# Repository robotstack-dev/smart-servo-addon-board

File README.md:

# Smart Servo Add-on Board

This repository contains the hardware design files and documentation for the Smart Servo Add-On Board.

[**Buy on Tindie**](https://www.tindie.com/products/robotstack/smart-servo-addon-board/)

> **Note:** This is an early version of the board. While it has been tested with several servo models, bugs may exist. Please report any issues you encounter.

## Description

This board allows wireless control different TTL smart servos. I developed it to use with Seeed's Xiao esp32-s3 Microcontroller, but it should also work with Adafruit's QT-Py esp32-s3, and likely other esp32s. I've tested it with the following smart servos: Robotis XL430-W250, AX-12W, Feetech HL3930M, and briefly with Waveshare's ST3215. Firmware and Control Software are available in the links below.

<div style="text-align: center;">
    
</div>

## Features

- Wireless Control of Smart Servos
- Compatible with Seeed Xiao and Adafruit QT-Py Form Factor
- Connectors for:

  - Dynamixel X-Series
  - Dynamixel AX-Series
  - Feetech HLS-Series / Waveshare ST3215

  > (Likely compatible with other smart servos; check your servo's specs)

- Stemma QT / QWIIC connector for compatible daughter boards (ie. sensors)
- Breakout pins
- 6.5 to 12 Volt Supply Range (check servo documentation for requirements)
- On board 5V regulator for Microcontroller
- Reverse Polarity Protection
- Firmware and Control Software available

## Hardware Overview

The pinouts are determined by the microcontroller you use. This board was designed to be used with the Seeed Xiao ESP32-S3 or the Adafruit QT Py ESP32-S3. See their documentation for details.

> **Important**: Check your servo connector's pinouts before connecting! Connecting to the wrong connector could damage the board and your servo.

<div style="text-align: center;">

</div>

<div style="text-align: center;">
    
</div>

<div style="text-align: center;">
    
</div>

## Getting the Board

### Pre-assembled

Pre-assembled boards are available for purchase on Tindie:
[Buy on Tindie](https://www.tindie.com/products/robotstack/smart-servo-addon-board/)

### DIY

You can build this board yourself using the hardware design files in this repository.

## Firmware

Example firmware for this board is available in a separate Arduino library. You can find it here:
[Smart Servo Bridge](https://github.com/robotstack-dev/smart-servo-bridge)

The library can be used with or without this addon board, making it flexible for different applications.

## Control Software

Python SDKs enabling wireless control of your smart servos are available. They require use of these boards implementing the [Smart Servo Bridge](https://github.com/robotstack-dev/smart-servo-bridge) library, or similar:

- [FTServo Python Websockets](https://github.com/robotstack-dev/ftservo-python-websockets)
- [Dynamixel Python SDK Websockets](https://github.com/robotstack-dev/dynamixel-python-sdk-websockets)

Other smart servos will require similar modifications to their SDKs.

## Getting Started

1. Build or purchase the circuit.
2. Attach a Microcontroller (eg. Seeed Xiao esp32-s3, or Adafruit QT Py esp32-s3).
3. Upload firmware over USB.
4. Attach your smart servo to the correct connector, according to your servo pinout.
5. Attach a power supply between 6.5 and 12 Volts, according to your servo requirements.
6. Run one of the control software examples that corresponds with your servo.

## Contributing

Contributions are welcome! Here are some guidelines to help you get started:

### How to Contribute

1. Fork the repository and create your branch from `master`.
2. Clone your fork and make your changes.
3. Test your changes if possible.
4. Submit a pull request with a clear description of your changes.

### Code of Conduct

- Be respectful and considerate in your communications.
- Assume good intentions and be constructive in feedback.

### Reporting Issues

- Use the issue tracker to report bugs or request features.
- Provide as much detail as possible (steps to reproduce, expected behavior, etc.).

## Author

Nicholas Stedman

- [GitHub](https://github.com/nsted)
- [Tindie Store](https://www.tindie.com/stores/robotstack/)

## License

This project is licensed under the MIT License - see the [LICENSE.txt](LICENSE.txt) file for details.

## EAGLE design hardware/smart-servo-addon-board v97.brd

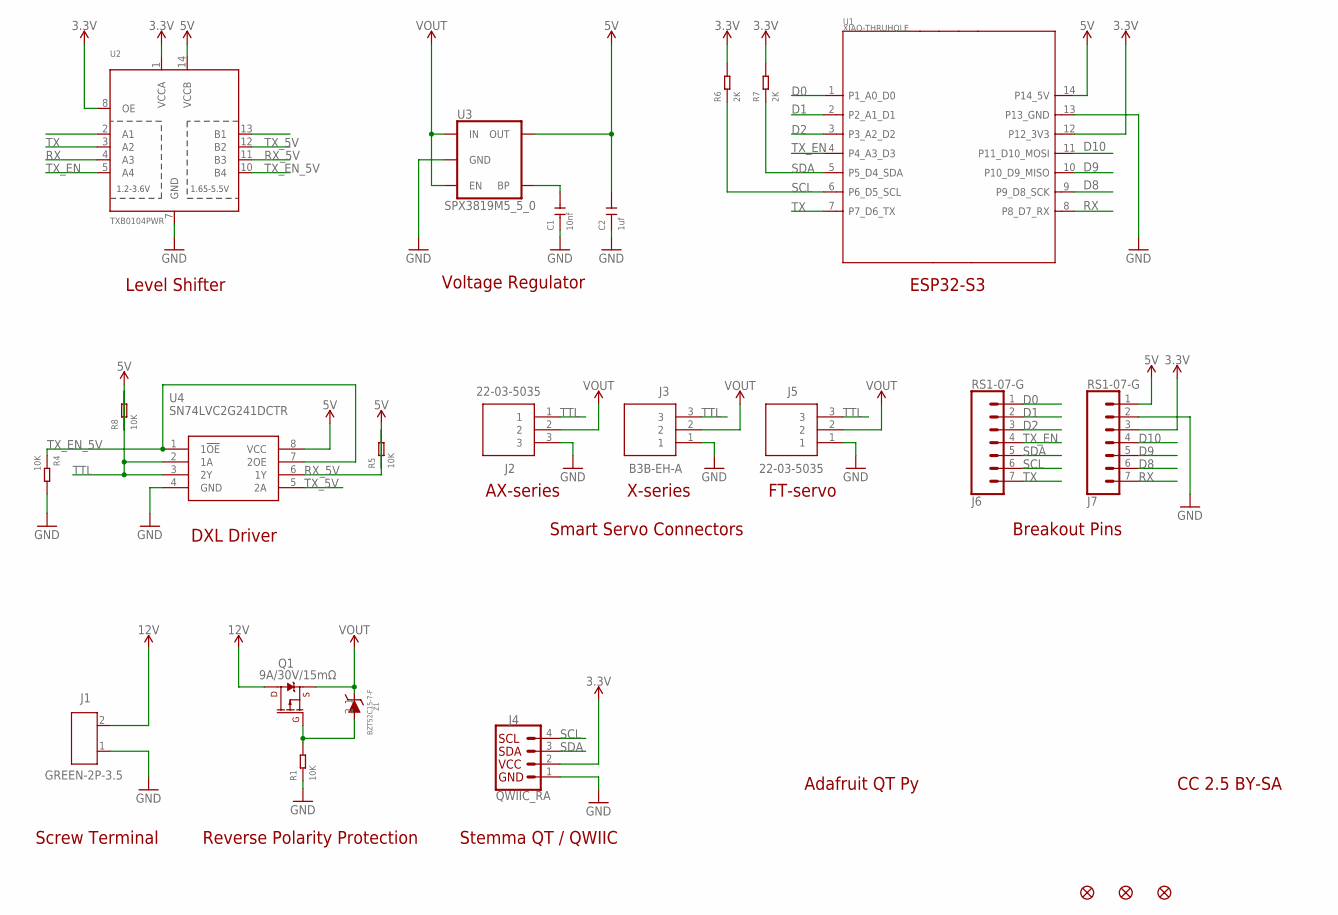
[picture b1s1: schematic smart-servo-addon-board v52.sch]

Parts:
C1: 10nf; C0603
C2: 1uf; C0603
FD4, FD5, FD6: FIDUCIAL""; FIDUCIAL_1MM
J1: GREEN-2P-3.5; H2-3.5-7.0X7.0MM
J2, J5: 22-03-5035; SHDR3W60P0X250_1X3_990X490X590
J3: B3B-EH-A; SHDR3W64P0X250_1X3_1000X380X60
J4: QWIIC_RA; JST04_1MM_RA
J6, J7: RS1-07-G; 1X07
Q1: 9A/30V/15mΩ; 8-POWERVDFN-3X3
R1, R4, R5, R8: 10K; R0603
R6, R7: 2K; R0603
U1: XIAO-THRUHOLE; XIAO-GENERIC-THRUHOLE-MODULE14P-2.54-21X17.8MM
U2: TXB0104PWR; TSSOP14
U3: SPX3819M5_5_0; SOT23-5
U4: SN74LVC2G241DCTR; SOP65P400X130-8N
Z1: BZT52C15-7-F; SOD3716X145N

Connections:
3.3V: J4.2, J7.3, R6.2, R7.2, U1.12 (P12_3V3), U2.1 (VCCA), U2.8 (OE)
5V: C2.2, J7.1, R5.1, R8.1, U1.14 (P14_5V), U2.14 (VCCB), U3.5 (OUT), U4.8 (VCC)
12V: J1.2, Q1.5@1 (D), Q1.5@2 (D), Q1.5@3 (D)
D0: J6.1, U1.1 (P1_A0_D0)
D1: J6.2, U1.2 (P2_A1_D1)
D2: J6.3, U1.3 (P3_A2_D2)
D8: J7.6, U1.9 (P9_D8_SCK)
D9: J7.5, U1.10 (P10_D9_MISO)
D10: J7.4, U1.11 (P11_D10_MOSI)
GND: C1.1, C2.1, J1.1, J2.3, J3.1, J4.1, J5.1, J7.2, R1.1, R4.2, U1.13 (P13_GND), U2.7 (GND), U3.2 (GND), U4.4 (GND)
unnamed: C1.2, U3.4 (BP)
unnamed: Q1.4 (G), R1.2, Z1.2 (A)
RX: J7.7, U1.8 (P8_D7_RX), U2.4 (A3)
RX_5V: R5.2, U2.11 (B3), U4.6 (1Y)
SCL: J4.4, J6.6, R6.1, U1.6 (P6_D5_SCL)
SDA: J4.3, J6.5, R7.1, U1.5 (P5_D4_SDA)
TTL: J2.1, J3.3, J5.3, R8.2, U4.2 (1A), U4.3 (2Y)
TX: J6.7, U1.7 (P7_D6_TX), U2.3 (A2)
TX_5V: U2.12 (B2), U4.5 (2A)
TX_EN: J6.4, U1.4 (P4_A3_D3), U2.5 (A4)
TX_EN_5V: R4.1, U2.10 (B4), U4.1 (1!OE), U4.7 (2OE)
VOUT: J2.2, J3.2, J5.2, Q1.1 (S), Q1.2 (S), Q1.3 (S), U3.1 (IN), U3.3 (EN), Z1.1 (K)

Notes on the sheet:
ESP32-S3
Smart Servo Connectors
Level Shifter
DXL Driver
Screw Terminal
Stemma QT / QWIIC
Voltage Regulator
Breakout Pins
X-series
FT-servo
AX-series
Reverse Polarity Protection
Adafruit QT Py
CC 2.5 BY-SA

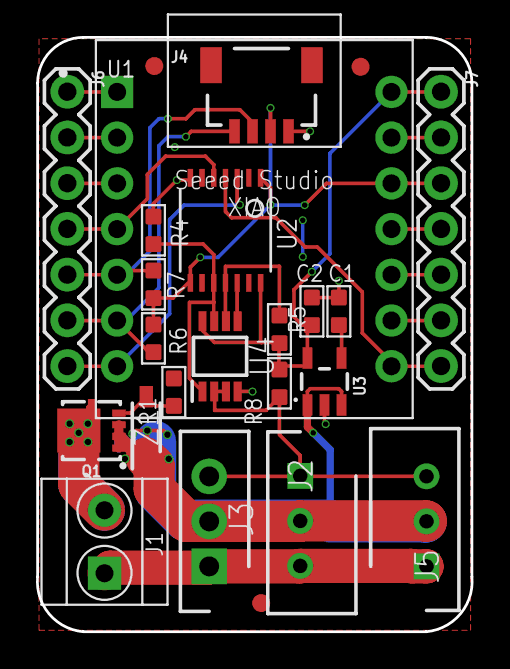
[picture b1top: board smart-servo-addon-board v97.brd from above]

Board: 2 copper layers, 24.2 x 33.0 mm, 24 parts (0 on the bottom side), 22 nets.

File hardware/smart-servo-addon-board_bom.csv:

Comment,Designator,Footprint,LCSC Part #
1uf,C2,C0603,
2K,R6 R7,R0603,
9A/30V/15mΩ,Q1,8-POWERVDFN-3X3,
10K,R1 R4 R5 R8,R0603,
10nf,C1,C0603,
22-03-5035,J2 J5,SHDR3W60P0X250_1X3_990X490X590,
B3B-EH-A,J3,SHDR3W64P0X250_1X3_1000X380X60,
BZT52C15-7-F,Z1,SOD3716X145N,
FIDUCIAL"",FD4 FD5 FD6,FIDUCIAL_1MM,
GREEN-2P-3.5,J1,H2-3.5-7.0X7.0MM,
QWIIC_RA,J4,JST04_1MM_RA,
RS1-07-G
,J6 J7,1X07,
SN74LVC2G241DCTR,U4,SOP65P400X130-8N,
SPX3819M5_5_0,U3,SOT23-5,
TXB0104PWR,U2,TSSOP14,
XIAO-THRUHOLE,U1,XIAO-GENERIC-THRUHOLE-MODULE14P-2.54-21X17.8MM,

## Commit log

2025-06-04 Initial commit: Project structure setup
2025-06-06 Update README with new features, images, and Tindie links.
2025-06-06 Add author information to README
2025-06-06 Update contributing section in README

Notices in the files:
parts and their libraries:
SparkFun-PowerSymbols: Licensing: Creative Commons ShareAlike 4.0 International - https://creativecommons.org/licenses/by-sa/4.0
